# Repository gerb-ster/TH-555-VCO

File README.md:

# Thomas Henry 555 VCO

The famous VCO module by Thomas Henry based on the 555 timer IC. This was the first module I ever designed a PCB for, which, in hindsight, was not the smartest move. It took me quit a while to get it bug-free, but now that it works, I love it! Over the years I read a lot of articles and booklets by Thomas Henry and if you’re into this synth diy stuff, I highly recommend checking out him and his work. If you want to build/buy one yourself, there is also an excellent version out there by a guy named Fonitronik, there is a link below.

## Status: Finished

- done: first schematic & board design
- done: breadboard and test
- done: design frontpanel
- done: order PCB and build prototype

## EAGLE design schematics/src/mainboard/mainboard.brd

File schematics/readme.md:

## Disclaimer

The files/schematics found in this folder are made with Eagle CAD v9.6.2.

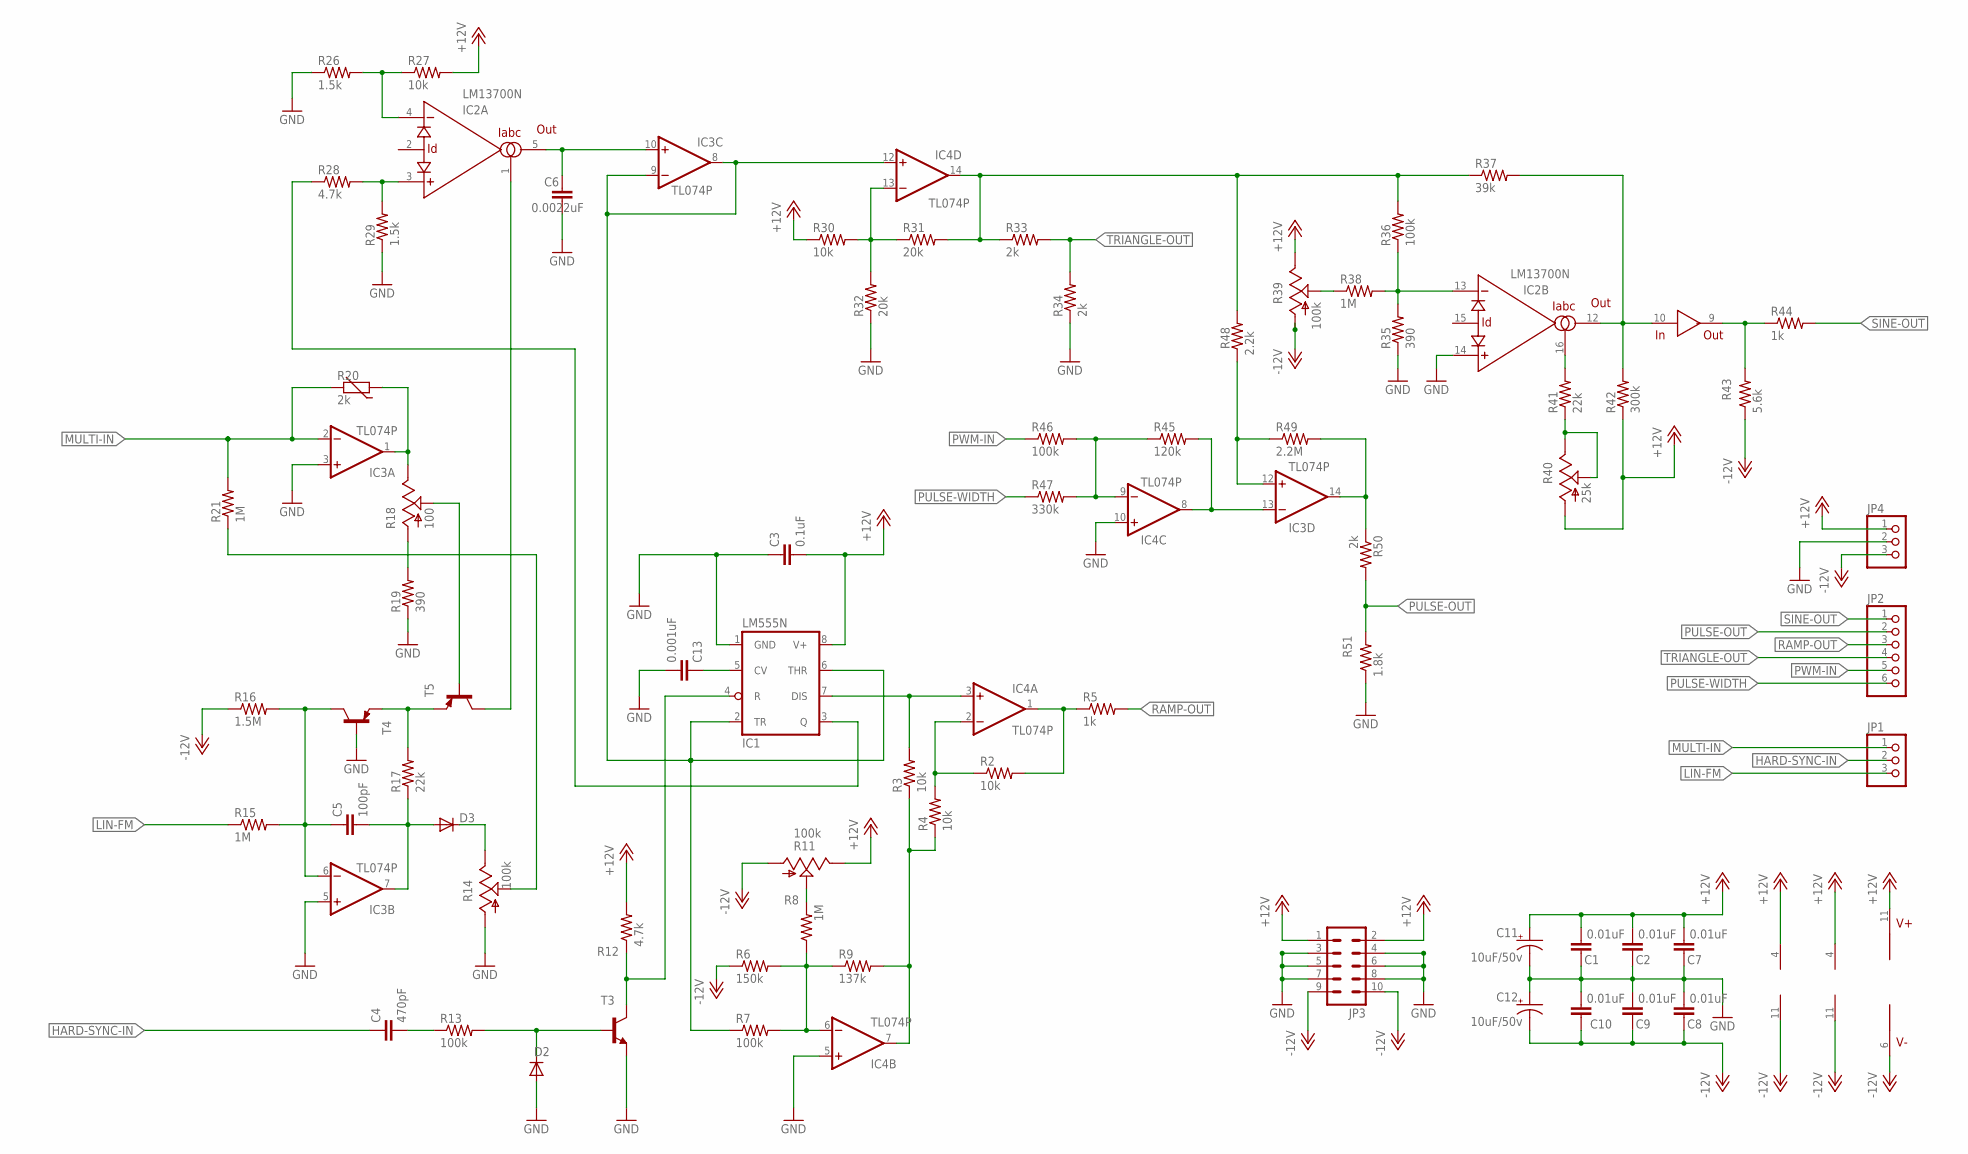
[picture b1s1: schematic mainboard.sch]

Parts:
C1, C2, C7, C8, C9, C10: 0.01uF; C050-024X044
C3: 0.1uF; C050-024X044
C4: 470pF; C050-024X044
C5: 100pF; C050-024X044
C6: 0.0022uF; C050-025X075
C11, C12: 10uF/50v; E2,5-6
C13: 0.001uF; C050-024X044
D2, D3: 1N4148DO35-7; DO35-7
IC1: LM555N; DIL08
IC2: LM13700N; DIL16
IC3, IC4: TL074P; DIL14
JP1, JP4: PINHD-1X3; 1X03
JP2: PINHD-1X6; 1X06
JP3: ML10
R2, R3, R4, R27, R30: 10k; 0204/7
R5, R44: 1k; 0204/7
R6: 150k; 0204/7
R7, R13, R36, R46: 100k; 0204/7
R8, R15, R21, R38: 1M; 0204/7
R9: 137k; 0204/7
R11, R14, R39: 100k; RJ9W
R12, R28: 4.7k; 0204/7
R16: 1.5M; 0204/7
R17, R41: 22k; 0204/7
R18: 100; RJ9W
R19, R35: 390; 0204/7
R20: 2k; R-5
R26, R29: 1.5k; 0204/7
R31, R32: 20k; 0204/7
R33, R34, R50: 2k; 0204/7
R37: 39k; 0204/7
R40: 25k; RJ9W
R42: 300k; 0204/7
R43: 5.6k; 0204/7
R45: 120k; 0204/7
R47: 330k; 0204/7
R48: 2.2k; 0204/7
R49: 2.2M; 0204/7
R51: 1.8k; 0204/7
T3: 2N3904-NPN-TO92-EBC; TO92-EBC
T4, T5: 2N3906-PNP-TO92-EBC; TO92-EBC

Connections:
+12V: C1.2, C2.2, C3.2, C7.2, C11.+, IC1.8 (V+), IC2.11 (V+), IC3.4 (V+), IC4.4 (V+), JP3.1, JP3.2, JP4.1, R11.E, R12.2, R27.2, R30.1, R39.E, R40.A, R42.1
-12V: C8.1, C9.1, C10.1, C12.-, IC2.6 (V-), IC3.11 (V-), IC4.11 (V-), JP3.9, JP3.10, JP4.3, R6.1, R11.A, R16.1, R39.A, R43.1
GND: C1.1, C2.1, C3.1, C6.2, C7.1, C8.2, C9.2, C10.2, C11.-, C12.+, C13.1, D2.A, IC1.1 (GND), IC2.14 (+IN), IC3.3 (+IN), IC3.5 (+IN), IC4.5 (+IN), IC4.10 (+IN), JP3.3, JP3.4, JP3.5, JP3.6, JP3.7, JP3.8, JP4.2, R14.A, R19.1, R26.1, R29.1, R32.1, R34.1, R35.1, R51.1, T3.E, T4.B
HARD-SYNC-IN: C4.1, JP1.2
LIN-FM: JP1.3, R15.1
MULTI-IN: IC3.2 (-IN), JP1.1, R20.2, R21.2
unnamed: IC1.7 (DIS), IC4.3 (+IN), R3.2
unnamed: IC4.2 (-IN), R2.1, R4.2
unnamed: IC4.1 (OUT), R2.2, R5.1
unnamed: IC4.7 (OUT), R3.1, R4.1, R9.2
unnamed: IC4.6 (-IN), R6.2, R7.2, R8.1, R9.1
unnamed: R38.1, R39.S
unnamed: C5.1, IC3.6 (-IN), R15.2, R16.2, T4.C
unnamed: R8.2, R11.S
unnamed: C5.2, D3.A, IC3.7 (OUT), R17.1
unnamed: C4.2, R13.1
unnamed: D2.C, R13.2, T3.B
unnamed: IC1.4 (R), R12.1, T3.C
unnamed: R17.2, T4.E, T5.E
unnamed: D3.C, R14.E
unnamed: R14.S, R21.1
unnamed: IC3.1 (OUT), R18.E, R20.1
unnamed: R18.S, T5.B
unnamed: IC2.1 (IABC), T5.C
unnamed: R18.A, R19.2
unnamed: IC2.3 (+IN), R28.2, R29.2
unnamed: IC1.3 (Q), R28.1
unnamed: IC2.4 (-IN), R26.2, R27.1
unnamed: C6.1, IC2.5 (OUT), IC3.10 (+IN)
unnamed: IC1.2 (TR), IC1.6 (THR), IC3.8 (OUT), IC3.9 (-IN), IC4.12 (+IN), R7.1
unnamed: IC4.13 (-IN), R30.2, R31.1, R32.2
unnamed: IC2.13 (-IN), R35.2, R36.1, R38.2
unnamed: IC4.14 (OUT), R31.2, R33.1, R36.2, R37.1, R48.2
unnamed: IC2.16 (IABC), R41.2
unnamed: R40.E, R40.S, R41.1
unnamed: IC2.10 (IN), IC2.12 (OUT), R37.2, R42.2
unnamed: IC2.9 (OUT), R43.2, R44.1
unnamed: IC3.13 (-IN), IC4.8 (OUT), R45.2
unnamed: C13.2, IC1.5 (CV)
unnamed: IC4.9 (-IN), R45.1, R46.2, R47.2
unnamed: IC3.12 (+IN), R48.1, R49.1
unnamed: IC3.14 (OUT), R49.2, R50.1
PULSE-OUT: JP2.2, R50.2, R51.2
PULSE-WIDTH: JP2.6, R47.1
PWM-IN: JP2.5, R46.1
RAMP-OUT: JP2.3, R5.2
SINE-OUT: JP2.1, R44.2
TRIANGLE-OUT: JP2.4, R33.2, R34.2

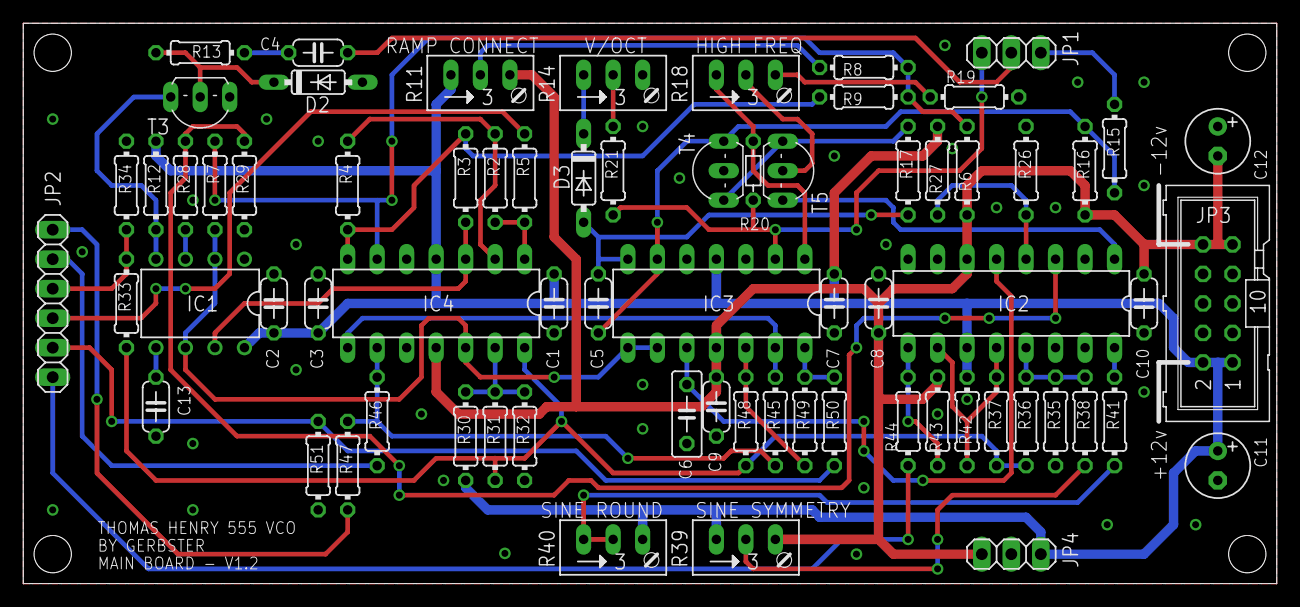
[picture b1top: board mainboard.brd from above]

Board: 2 copper layers, 108.0 x 48.3 mm, 71 parts (0 on the bottom side), 48 nets.

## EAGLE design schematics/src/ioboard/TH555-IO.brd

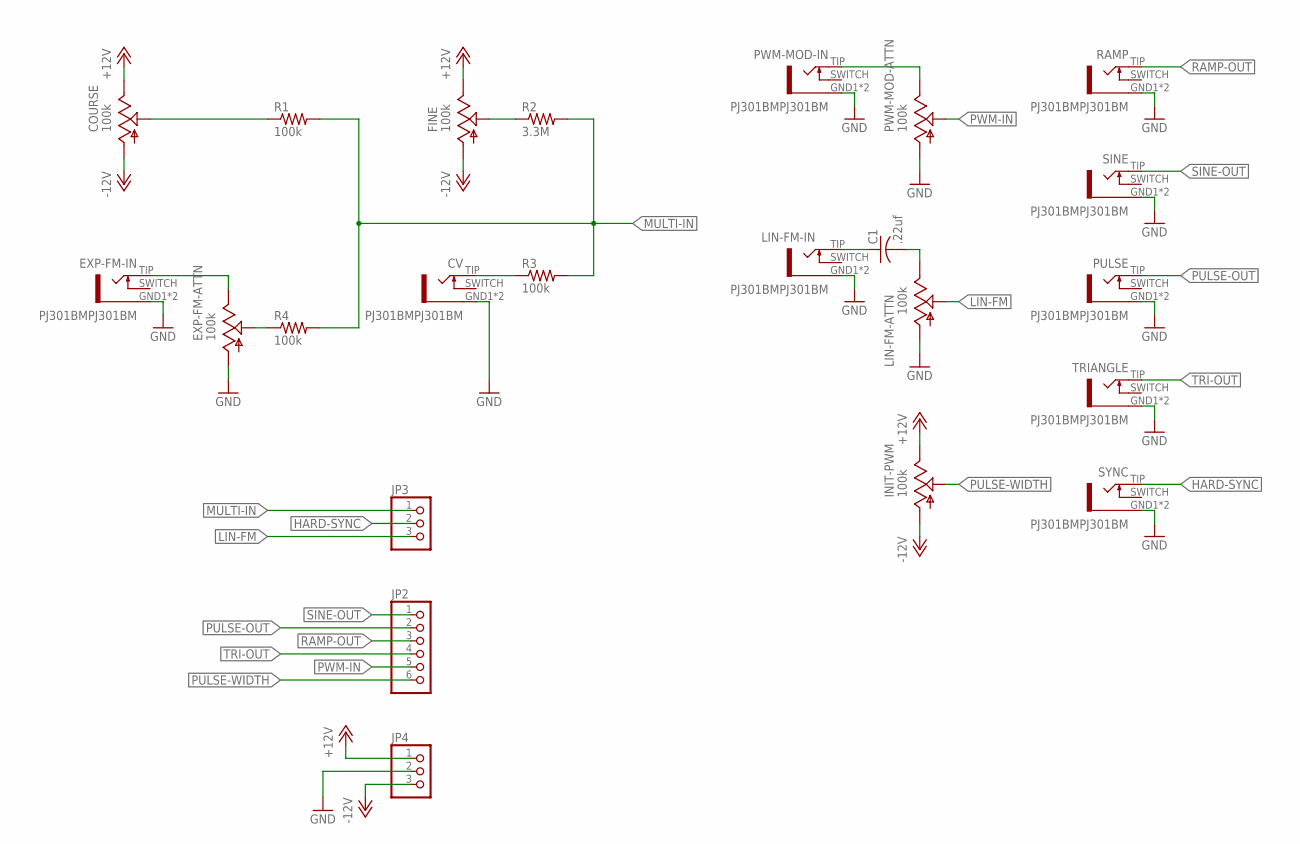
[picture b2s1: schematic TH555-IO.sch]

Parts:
C1: .22uf; C050-024X044
COURSE: 100k; EVUF
CV: PJ301BMPJ301BM; PJ301BM
EXP-FM-ATTN: 100k; EVUF
EXP-FM-IN: PJ301BMPJ301BM; PJ301BM
FINE: 100k; EVUF
INIT-PWM: 100k; EVUF
JP2: PINHD-1X6; 1X06
JP3, JP4: PINHD-1X3; 1X03
LIN-FM-ATTN: 100k; EVUF
LIN-FM-IN: PJ301BMPJ301BM; PJ301BM
PULSE: PJ301BMPJ301BM; PJ301BM
PWM-MOD-ATTN: 100k; EVUF
PWM-MOD-IN: PJ301BMPJ301BM; PJ301BM
R1, R3, R4: 100k; 0207/10
R2: 3.3M; 0207/10
RAMP: PJ301BMPJ301BM; PJ301BM
SINE: PJ301BMPJ301BM; PJ301BM
SYNC: PJ301BMPJ301BM; PJ301BM
TRIANGLE: PJ301BMPJ301BM; PJ301BM

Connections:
1V/OCT: CV.TIP (3), R3.1
+12V: COURSE.3 (E), FINE.3 (E), INIT-PWM.3 (E), JP4.1
-12V: COURSE.1 (A), FINE.1 (A), INIT-PWM.1 (A), JP4.3
COARSE: COURSE.2 (S), R1.1
EXP-FM: EXP-FM-ATTN.3 (E), EXP-FM-IN.TIP (3)
EXP-FM-ATTN: EXP-FM-ATTN.2 (S), R4.1
FINE: FINE.2 (S), R2.1
GND: CV.GND1 (5), CV.GND2 (5), EXP-FM-ATTN.1 (A), EXP-FM-IN.GND1 (5), EXP-FM-IN.GND2 (5), JP4.2, LIN-FM-ATTN.1 (A), LIN-FM-IN.GND1 (5), LIN-FM-IN.GND2 (5), PULSE.GND1 (5), PULSE.GND2 (5), PWM-MOD-ATTN.1 (A), PWM-MOD-IN.GND1 (5), PWM-MOD-IN.GND2 (5), RAMP.GND1 (5), RAMP.GND2 (5), SINE.GND1 (5), SINE.GND2 (5), SYNC.GND1 (5), SYNC.GND2 (5), TRIANGLE.GND1 (5), TRIANGLE.GND2 (5)
HARD-SYNC: JP3.2, SYNC.TIP (3)
LIN-FM: JP3.3, LIN-FM-ATTN.2 (S)
MULTI-IN: JP3.1, R1.2, R2.2, R3.2, R4.2
unnamed: PWM-MOD-ATTN.3 (E), PWM-MOD-IN.TIP (3)
unnamed: C1.2, LIN-FM-ATTN.3 (E)
unnamed: C1.1, LIN-FM-IN.TIP (3)
PULSE-OUT: JP2.2, PULSE.TIP (3)
PULSE-WIDTH: INIT-PWM.2 (S), JP2.6
PWM-IN: JP2.5, PWM-MOD-ATTN.2 (S)
RAMP-OUT: JP2.3, RAMP.TIP (3)
SINE-OUT: JP2.1, SINE.TIP (3)
TRI-OUT: JP2.4, TRIANGLE.TIP (3)

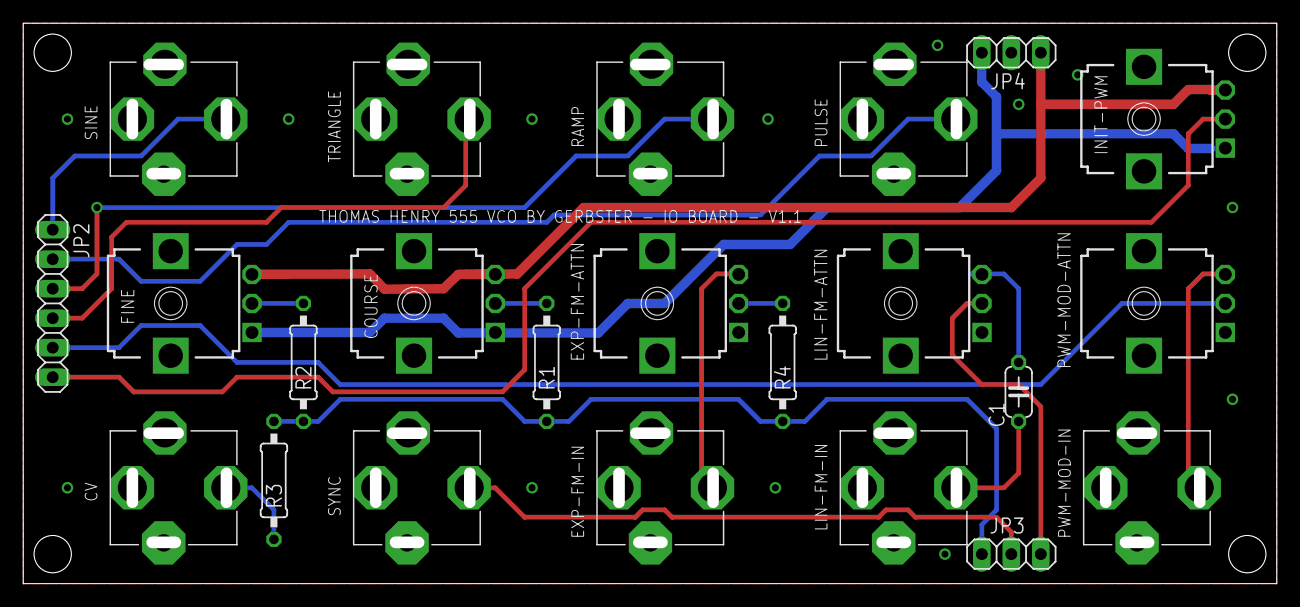
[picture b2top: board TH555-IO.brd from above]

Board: 2 copper layers, 107.0 x 47.3 mm, 23 parts (0 on the bottom side), 20 nets.

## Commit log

2021-05-06 some files
2021-05-06 gitignore
2021-05-07 Added files & structure
2021-05-10 Added Status
2021-05-11 Added Status & Images
2021-08-06 Updated some schematics and docs
2021-08-10 Fixed some bugs and updated documentation
2022-04-20 Some updates & bugfixes
2022-04-22 Fixed schematics & descriptions
2022-05-17 Updated Firmware
2022-05-18 Updated Faceplates
2022-05-18 Fixed issues
2022-05-21 Fixed schematics
2022-05-28 General updates
